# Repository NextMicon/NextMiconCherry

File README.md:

# NextMicon FPGA

**This repository has been split into per-board repositories and is archived.**
Development continues at
[NextMicon/cherry](https://github.com/NextMicon/cherry),
[NextMicon/grape](https://github.com/NextMicon/grape), and
[NextMicon/melon](https://github.com/NextMicon/melon).

NextMicon is a family of open-source FPGA development boards. Choose the compact Cherry to get started, or Grape for a larger FPGA and more I/O.

|       | [🍒 Cherry](boards/cherry/) | [🍇 Grape](boards/grape/)     | [🍈 Melon](boards/melon/)      |
| ----- | -------------------------- | ---------------------------- | ----------------------------- |
| FPGA  | Lattice iCE40HX8K-BG121    | AMD Spartan-7 XC7S50-CSGA324 | AMD Artix-7 XC7A100T-1FGG676C |
| Logic | 7,680 (4-input LUT)        | 32,600 (6-input LUT)         | 63,400 (6-input LUT)          |
| BRAM  | 128 Kbit                   | 2,700 Kbit                   | 4,860 Kbit                    |
| DSP   | —                          | 120                          | 240                           |
| GPIO  | 64                         | 128                          | 256                           |

## 🍒 NextMicon Cherry

**A compact board for learning and small projects.** Cherry is built around the Lattice iCE40HX8K-BG121, with 7,680 LUTs, 64 GPIO pins, native USB Full-Speed, and protected `boot` plus writable `user` FPGA images. The repository includes its KiCad PCB design, fabrication outputs, bootloader HDL, and host application.

[Explore Cherry →](boards/cherry/)

Cherry firmware can be managed with the [`nmb` CLI](flash/cli/README.md) or the
[Web Serial flasher](flash/web/README.md).

## 🍇 NextMicon Grape

**A mid-range board for multi-channel phased-array acoustic field generation.** Grape uses the AMD Spartan-7 XC7S50-CSGA324 with 128 GPIO outputs and a 128-Mbit QSPI flash. Firmware is built and programmed with a fully open-source Yosys, nextpnr-xilinx, Project X-Ray, and openFPGALoader stack. Its schematic and PCB are being migrated from the earlier Artix-7 prototype.

[Explore Grape →](boards/grape/)

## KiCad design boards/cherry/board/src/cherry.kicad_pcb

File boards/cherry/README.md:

# 🍒 NextMicon Cherry 🍒

FPGA Board for Beginners

## Repository layout

- [`board`](board/): KiCad design and fabrication outputs
- [`breakout`](breakout/): PMod breakout board
- [`firmware`](firmware/): FPGA HDL and constraints

## Schematic

## Specs

- FPGA: Lattice iCE40HX8K-BG121 (7680 LUTs, 9x9mm, 0.8mm pitch)
- GPIO: 64 pins (3.3V logic)
- PLL: 2x sysCLOCK PLL, external reference inputs broken out on J3 position 22 (PLL0_IN/PLL1_IN)
- Clock: 48MHz
- Flash: 32Mbit SPI Flash (3.5 MiB user-data area)
- Power: USB 5V → 3.3V → 1.2V
- Signal: 3.3V
- USB ESD Protection
- Switch: CRESET_B reset / USER buttons
- LED: PWR / PROG / USER0-USER3
- Board: 61mm x 31mm, 4-layer FR4

## Pinout

J2 and J3 are standard 2x24 headers. Each connector position `k` (1..24) has an
inner-row pad `2k-1` (odd) and an outer-row pad `2k` (even); the two rows carry
independent signals.

GPIOs are grouped in blocks of eight: D0-D3 sit on the inner row and D4-D7 sit
directly opposite on the outer row of the same four positions, so every block
forms one contiguous 2x4 window flanked by GND (inner) / 3V3 (outer) columns.
J2 carries GPIO_1..32 and J3 carries GPIO_33..64.

J2 (bottom edge, position 1 = USB side):

| Position | Inner row (odd pads) | Outer row (even pads) |
| -------- | -------------------- | --------------------- |
| 1        | 5V                   | 5V                    |
| 2        | 3V3                  | 3V3                   |
| 3        | CRESET_B             | 3V3                   |
| 4        | GND                  | 3V3                   |
| 5-8      | GPIO_1..4            | GPIO_5..8             |
| 9        | GND                  | 3V3                   |
| 10-13    | GPIO_9..12           | GPIO_13..16           |
| 14       | GND                  | 3V3                   |
| 15-18    | GPIO_17..20          | GPIO_21..24           |
| 19       | GND                  | 3V3                   |
| 20-23    | GPIO_25..28          | GPIO_29..32           |
| 24       | GND                  | 3V3                   |

J3 (top edge, position 24 = USB side):

| Position | Inner row (odd pads) | Outer row (even pads) |
| -------- | -------------------- | --------------------- |
| 1        | GND                  | 3V3                   |
| 2-5      | GPIO_33..36          | GPIO_37..40           |
| 6        | GND                  | 3V3                   |
| 7-10     | GPIO_41..44          | GPIO_45..48           |
| 11       | GND                  | 3V3                   |
| 12-15    | GPIO_49..52          | GPIO_53..56           |
| 16       | GND                  | 3V3                   |
| 17-20    | GPIO_57..60          | GPIO_61..64           |
| 21       | GND                  | 3V3                   |
| 22       | PLL0_IN              | PLL1_IN               |
| 23       | 3V3                  | 3V3                   |
| 24       | 5V                   | 5V                    |

| Header                          | Pins                                                                           |
| ------------------------------- | ------------------------------------------------------------------------------ |
| J4 (right edge, pin 1 = bottom) | 1 = GND, 2 = CRESET_B, 3 = QSPI_CS_B, 4 = QSPI_SCK, 5 = QSPI_IO0, 6 = QSPI_IO1 |

The breakout board ([`breakout/`](breakout/)) accepts the Cherry via female
pin sockets (J2/J3/J4 plug straight in) and brings the 64 GPIOs out as eight
standard Pmod ports (8 GPIO each), plus an SPI header and a power/CRESET
utility header.

## BOM

| Ref   | Part                                     | Package         | Description              | Cost  | Buy                                                                                           |
| ----- | ---------------------------------------- | --------------- | ------------------------ | ----- | --------------------------------------------------------------------------------------------- |
| U1    | [W25Q32JVSSIQ](../../parts/W25Q32JV.pdf) | SOIC-8 208mil   | 32Mbit SPI Flash         | -     | [digikey](https://www.digikey.com/en/products/result?keywords=W25Q32JVSSIQ)                   |
| U2    | [iCE40HX8K-BG121](../../parts/iCE40.pdf) | caBGA-121 0.8mm | FPGA 7680 LUTs           | -     | [digikey](https://www.digikey.com/en/products/result?keywords=ICE40HX8K-BG121)                |
| U3-U4 | [TPS62A02](../../parts/TPS62A02.pdf)     | SOT-23-6        | 2A DC-DC Converter       | $0.25 | [digikey](https://www.digikey.jp/ja/products/detail/texas-instruments/TPS62A02PDDCR/22147220) |
| D1    | USBLC6-2SC6                              | SOT-23-6        | USB ESD protection       | -     | [digikey](https://www.digikey.jp/ja/products/result?keywords=USBLC6-2SC6)                     |
| X1    | OXETDLJANF-48.000000MHz                  | 3.2x2.5mm       | 48MHz XO                 | -     | generic                                                                                       |
| FB1   | GZ2012D601TF                             | 0805            | Ferrite bead (USB VBUS)  | -     | [lcsc](https://www.lcsc.com/search?q=GZ2012D601TF)                                            |
| J1    | USB4085-GF-A                             | SMD 16pin       | USB-C connector          | $1.01 | [digikey](https://www.digikey.jp/ja/products/detail/gct/USB4085-GF-A/9859662)                 |
| J2-J3 | Pin header 2x24                          | 2.54mm Pitch    | GPIO                     | -     | generic                                                                                       |
| J4    | Pin header 1x06                          | 2.54mm Pitch    | External SPI programming | -     | generic                                                                                       |
### Passives

| Ref                       | Value                | Pkg  | Qty |
| ------------------------- | -------------------- | ---- | --- |
| C1,C3,C5,C14,C17          | 10uF                 | 0805 | 5   |
| C4,C6                     | 22uF                 | 0805 | 2   |
| C2,C7-C13,C15-C16,C18-C24 | 100nF               | 0402 | 17  |
| L1-L2                     | TFM201208ALD-1R0MTCA | 0805 | 2   |
| R1-R2                     | 5.1k                 | 0402 | 2   |
| R3,R5-R6                  | 100k                 | 0402 | 3   |
| R4                        | 22k                  | 0402 | 1   |
| R7                        | 1.5k                 | 0402 | 1   |
| R8-R9                     | 68                   | 0402 | 2   |
| R10-R13,R16-R17,R22-R23   | 10k                  | 0402 | 8   |
| R14,R18-R21,R24-R25       | 1k                   | 0402 | 7   |
| R15                       | 100                  | 0402 | 1   |
| D2-D4,D6-D7               | KT-0603R             | 0603 | 5   |
| D5                        | LED_AMBER_0603       | 0603 | 1   |
| SW1-SW2                   | TS-1187A-B-A-B       | SMD  | 2   |
| JP1-JP2                   | Solder jumper        | SMD  | 2   |

## Build

Toolchain: [Yosys](https://github.com/YosysHQ/yosys) + [nextpnr-ice40](https://github.com/YosysHQ/nextpnr) + [icestorm](https://github.com/YosysHQ/icestorm)

The pin and timing constraint files are
[`firmware/cherry.pcf`](firmware/cherry.pcf) and
[`firmware/cherry.sdc`](firmware/cherry.sdc). Yosys produces the JSON netlist
and nextpnr consumes the PCF/SDC:

```bash
mkdir -p build
yosys -p 'synth_ice40 -top top -json build/top.json' rtl/top.v
nextpnr-ice40 --hx8k --package bg121 --freq 48 \
  --json build/top.json --pcf firmware/cherry.pcf --sdc firmware/cherry.sdc \
  --asc build/top.asc
icepack build/top.asc build/top.bin
```

Only ports present in the top-level HDL need to be used; nextpnr reports the
other PCF entries as harmless `unmatched constraint` warnings. Keep `clk_48m`
as an input. The commented SPI-flash constraints are intentionally reserved
because the flash and FPGA configuration controller share those four nets.

For recovery programming, power the board from USB and connect a 3.3V SPI
programmer to J4. Hold `CRESET_B` low while accessing the W25Q32, then release
it to boot the newly written image.

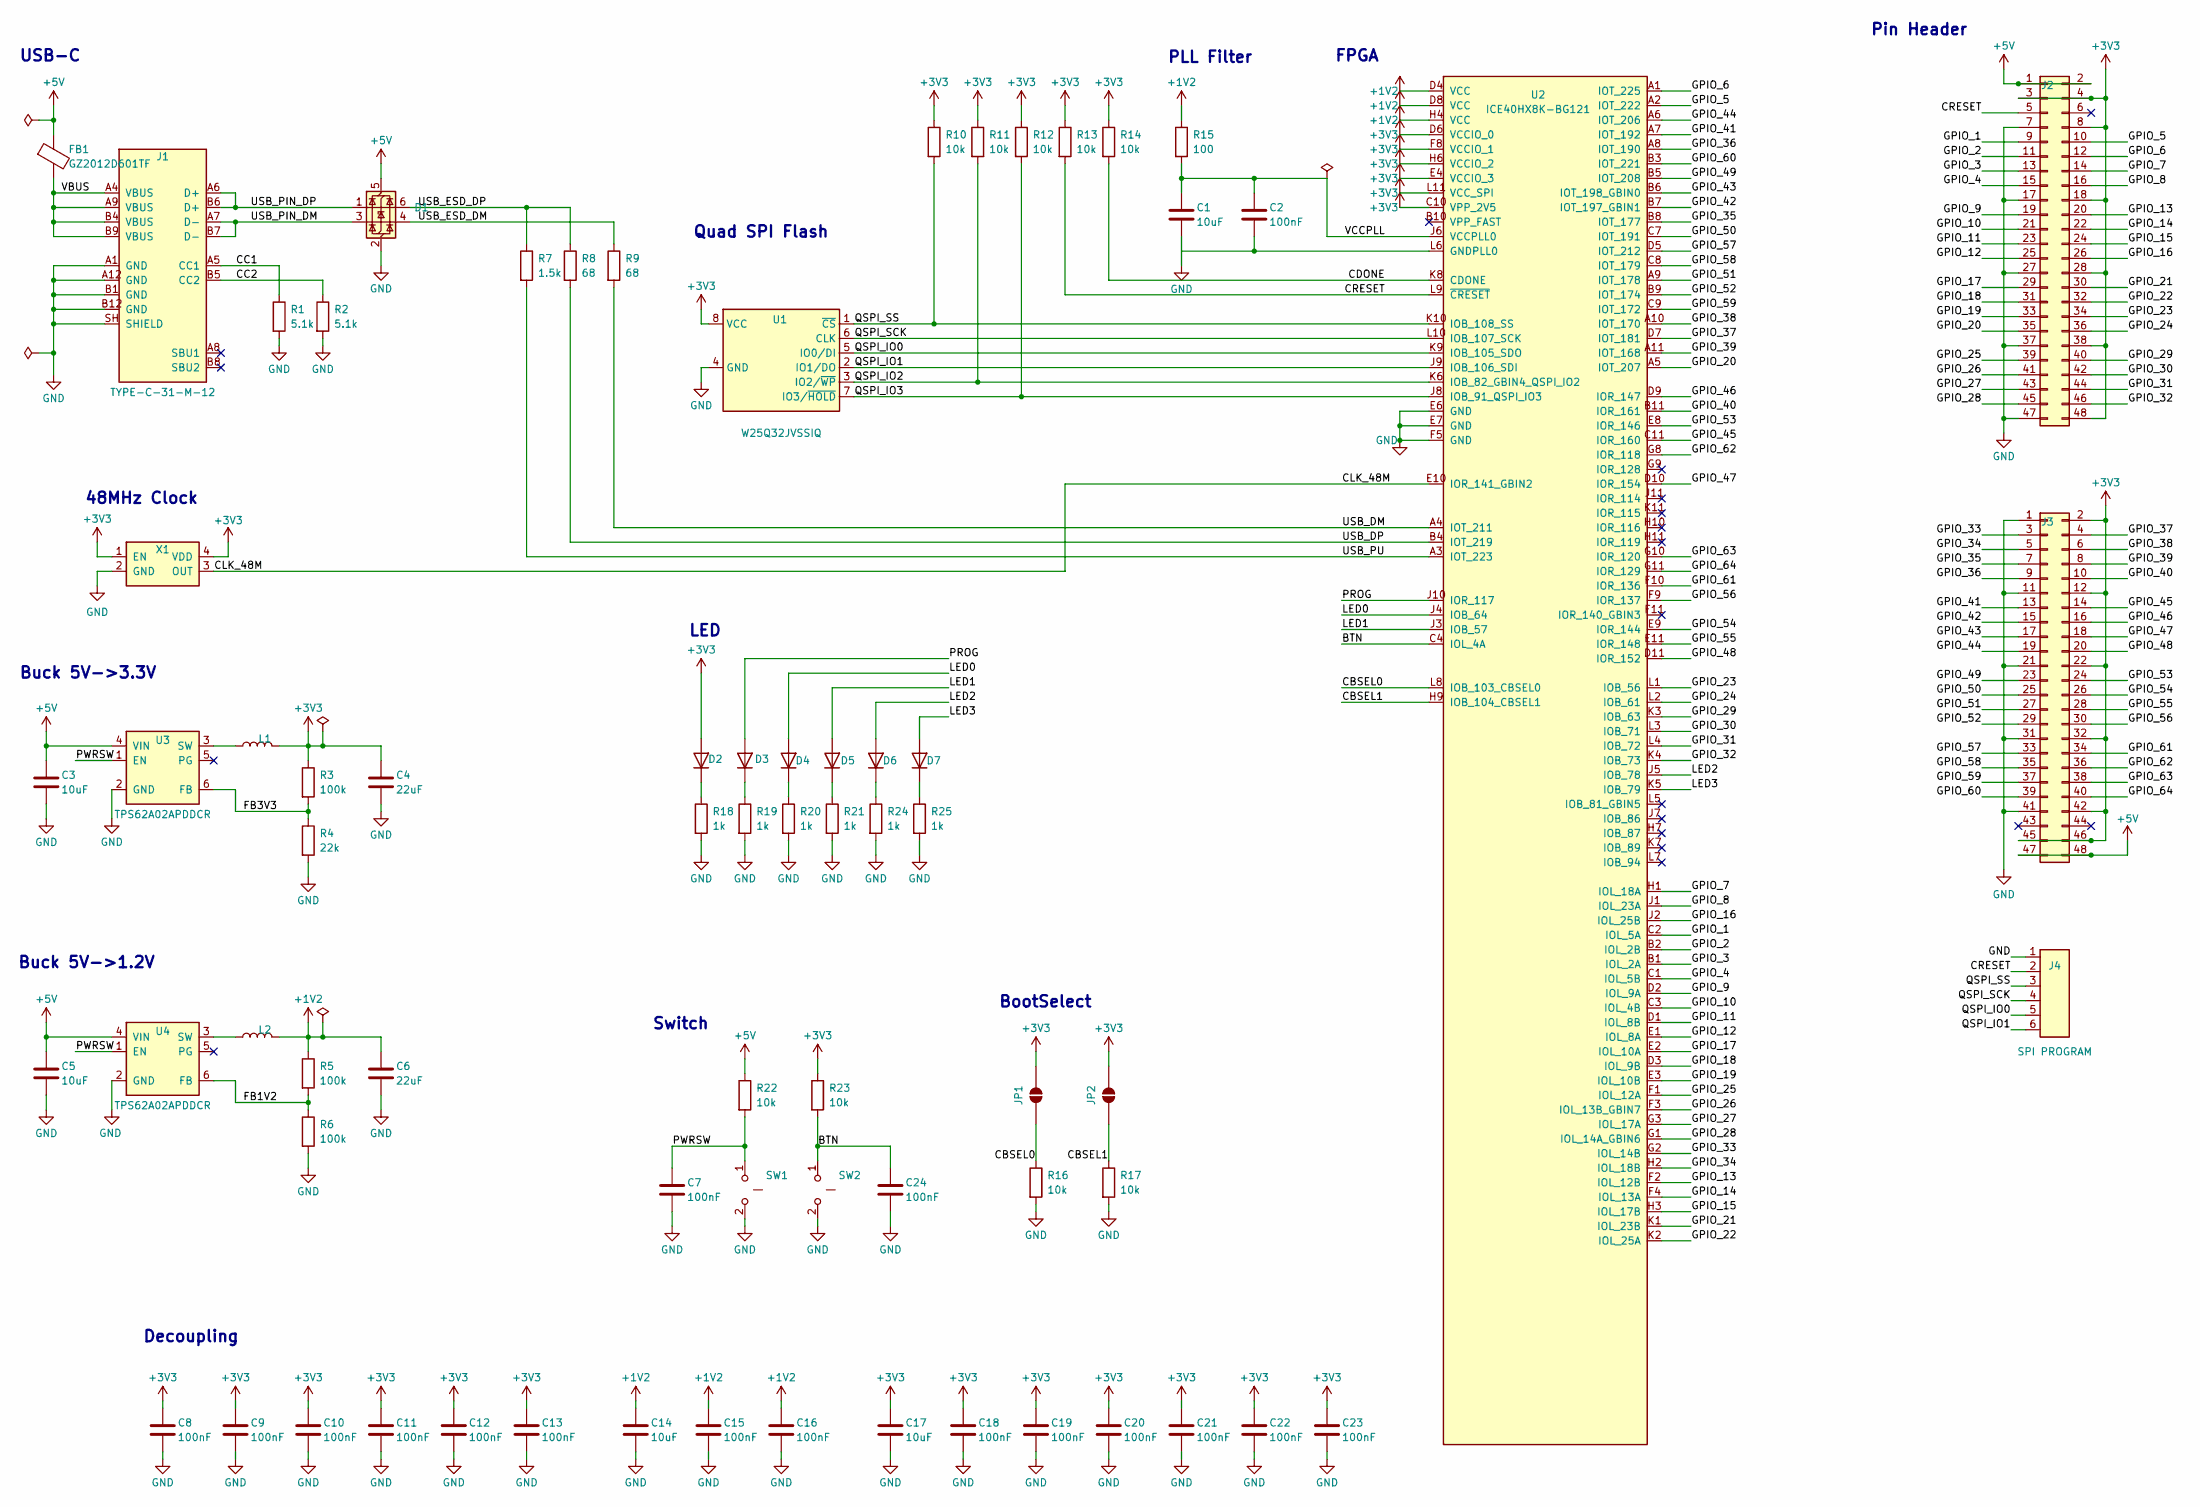
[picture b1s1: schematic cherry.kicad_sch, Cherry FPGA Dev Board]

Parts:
C1, C3, C5, C14, C17: 10uF; C_0805_2012Metric; LCSC C15850
C2, C7, C8, C9, C10, C11, C12, C13, C15, C16, C18, C19, C20, C21, C22, C23, C24: 100nF; C_0402_1005Metric; LCSC C1525
C4, C6: 22uF; C_0805_2012Metric; LCSC C45783
D1: USBLC6-2SC6; SOT-23-6; LCSC C2687116
D2, D3, D4, D6, D7: KT-0603R; LED_0603_1608Metric; LCSC C2286
D5: LED_AMBER_0603; LED_0603_1608Metric
FB1: GZ2012D601TF; L_0805_2012Metric; LCSC C1017
J1: TYPE-C-31-M-12; USB_C_Receptacle_Hroparts_TYPE-C-31-M-12; LCSC C165948
J2, J3: Conn_02x24_Odd_Even; PinHeader_2x24_P2.54mm_Vertical
J4: SPI PROGRAM; PinHeader_1x06_P2.54mm_Vertical
JP1, JP2: USER; SolderJumper-2_P1.3mm_Open_RoundedPad1.0x1.5mm
L1, L2: TFM201208ALD-1R0MTCA; L_TDK_TFM201208ALD; LCSC C433051
R1, R2: 5.1k; R_0402_1005Metric; LCSC C25905
R3, R5, R6: 100k; R_0402_1005Metric; LCSC C25741
R4: 22k; R_0402_1005Metric; LCSC C25768
R7: 1.5k; R_0402_1005Metric; LCSC C25117
R8, R9: 68; R_0402_1005Metric; LCSC C25117
R10, R11, R12, R13, R16, R17, R23: 10k; R_0402_1005Metric; LCSC C25744
R14: 10k; R_0402_1005Metric; LCSC C11702
R15: 100; R_0402_1005Metric; LCSC C25076
R18, R19, R20, R21, R24, R25: 1k; R_0402_1005Metric; LCSC C11702
R22: 10k; R_0402_1005Metric; LCSC C25741
SW1: TS-1187A-B-A-B; SW_Tactile_XKB_TS-1187A; LCSC C318884
SW2: USER; SW_Tactile_XKB_TS-1187A; LCSC C318884
U1: W25Q32JVSSIQ; SOIC-8_5.3x5.3mm_P1.27mm; LCSC C179173
U2: ICE40HX8K-BG121; BGA-121_9.0x9.0mm_Layout11x11_P0.8mm_Ball0.4mm_Pad0.35mm_NS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
U3, U4: TPS62A02APDDCR; SOT-23-6; LCSC C25687169
X1: OXETDLJANF-48.000000MHz; Oscillator_SMD_Taitien_OX_3.2x2.5mm; LCSC C5173414

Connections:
+1V2: C6.1, C14.1, C15.1, C16.1, L2.2, R5.1, R15.1, U2.D4 (VCC), U2.D8 (VCC), U2.H4 (VCC), U2.H8 (VCC)
+3V3: C4.1, C8.1, C9.1, C10.1, C11.1, C12.1, C13.1, C17.1, C18.1, C19.1, C20.1, C21.1, C22.1, C23.1, D2.2 (A), J2.3, J2.4, J2.8, J2.18, J2.28, J2.38, J2.48, J3.2, J3.12, J3.22, J3.32, J3.42, J3.45, J3.46, JP1.2 (B), JP2.2 (B), L1.2, R3.1, R10.1, R11.1, R12.1, R13.1, R14.1, R23.1, U1.8 (VCC), U2.C10 (VPP_2V5), U2.D6 (VCCIO_0), U2.E4 (VCCIO_3), U2.F8 (VCCIO_1), U2.G4 (VCCIO_3), U2.H6 (VCCIO_2), U2.L11 (VCC_SPI), X1.1 (EN), X1.4 (VDD)
+5V: C3.1, C5.1, D1.5 (VBUS), FB1.1, J2.1, J2.2, J3.47, J3.48, R22.1, U3.4 (VIN), U4.4 (VIN)
/BTN: C24.1, R23.2, SW2.1, U2.C4 (IOL_4A)
/CBSEL0: JP1.1 (A), R16.1, U2.L8 (IOB_103_CBSEL0)
/CBSEL1: JP2.1 (A), R17.1, U2.H9 (IOB_104_CBSEL1)
/CC1: J1.A5 (CC1), R1.1
/CC2: J1.B5 (CC2), R2.1
/CDONE: R14.2, U2.K8 (CDONE)
/CLK_48M: U2.E10 (IOR_141_GBIN2), X1.3 (OUT)
/CRESET: J2.5, J4.2, R13.2, U2.L9 (~CRESET)
/FB1V2: R5.2, R6.1, U4.6 (FB)
/FB3V3: R3.2, R4.1, U3.6 (FB)
/GPIO_1: J2.9, U2.C2 (IOL_5A)
/GPIO_2: J2.11, U2.B2 (IOL_2B)
/GPIO_3: J2.13, U2.B1 (IOL_2A)
/GPIO_4: J2.15, U2.C1 (IOL_5B)
/GPIO_5: J2.10, U2.A2 (IOT_222)
/GPIO_6: J2.12, U2.A1 (IOT_225)
/GPIO_7: J2.14, U2.H1 (IOL_18A)
/GPIO_8: J2.16, U2.J1 (IOL_23A)
/GPIO_9: J2.19, U2.D2 (IOL_9A)
/GPIO_10: J2.21, U2.C3 (IOL_4B)
/GPIO_11: J2.23, U2.D1 (IOL_8B)
/GPIO_12: J2.25, U2.E1 (IOL_8A)
/GPIO_13: J2.20, U2.F2 (IOL_12B)
/GPIO_14: J2.22, U2.F4 (IOL_13A)
/GPIO_15: J2.24, U2.H3 (IOL_17B)
/GPIO_16: J2.26, U2.J2 (IOL_25B)
/GPIO_17: J2.29, U2.E2 (IOL_10A)
/GPIO_18: J2.31, U2.D3 (IOL_9B)
/GPIO_19: J2.33, U2.E3 (IOL_10B)
/GPIO_20: J2.35, U2.A5 (IOT_207)
/GPIO_21: J2.30, U2.K1 (IOL_23B)
/GPIO_22: J2.32, U2.K2 (IOL_25A)
/GPIO_23: J2.34, U2.L1 (IOB_56)
/GPIO_24: J2.36, U2.L2 (IOB_61)
/GPIO_25: J2.39, U2.F1 (IOL_12A)
/GPIO_26: J2.41, U2.F3 (IOL_13B_GBIN7)
/GPIO_27: J2.43, U2.G3 (IOL_17A)
/GPIO_28: J2.45, U2.G1 (IOL_14A_GBIN6)
/GPIO_29: J2.40, U2.K3 (IOB_63)
/GPIO_30: J2.42, U2.L3 (IOB_71)
/GPIO_31: J2.44, U2.L4 (IOB_72)
/GPIO_32: J2.46, U2.K4 (IOB_73)
/GPIO_33: J3.3, U2.G2 (IOL_14B)
/GPIO_34: J3.5, U2.H2 (IOL_18B)
/GPIO_35: J3.7, U2.B8 (IOT_177)
/GPIO_36: J3.9, U2.A8 (IOT_190)
/GPIO_37: J3.4, U2.D7 (IOT_181)
/GPIO_38: J3.6, U2.A10 (IOT_170)
/GPIO_39: J3.8, U2.A11 (IOT_168)
/GPIO_40: J3.10, U2.B11 (IOR_161)
/GPIO_41: J3.13, U2.A7 (IOT_192)
/GPIO_42: J3.15, U2.B7 (IOT_197_GBIN1)
/GPIO_43: J3.17, U2.B6 (IOT_198_GBIN0)
/GPIO_44: J3.19, U2.A6 (IOT_206)
/GPIO_45: J3.14, U2.C11 (IOR_160)
/GPIO_46: J3.16, U2.D9 (IOR_147)
/GPIO_47: J3.18, U2.D10 (IOR_154)
/GPIO_48: J3.20, U2.D11 (IOR_152)
/GPIO_49: J3.23, U2.B5 (IOT_208)
/GPIO_50: J3.25, U2.C7 (IOT_191)
/GPIO_51: J3.27, U2.A9 (IOT_178)
/GPIO_52: J3.29, U2.B9 (IOT_174)
/GPIO_53: J3.24, U2.E8 (IOR_146)
/GPIO_54: J3.26, U2.E9 (IOR_144)
/GPIO_55: J3.28, U2.E11 (IOR_148)
/GPIO_56: J3.30, U2.F9 (IOR_137)
/GPIO_57: J3.33, U2.D5 (IOT_212)
/GPIO_58: J3.35, U2.C8 (IOT_179)
/GPIO_59: J3.37, U2.C9 (IOT_172)
/GPIO_60: J3.39, U2.B3 (IOT_221)
/GPIO_61: J3.34, U2.F10 (IOR_136)
/GPIO_62: J3.36, U2.G8 (IOR_118)
/GPIO_63: J3.38, U2.G10 (IOR_120)
/GPIO_64: J3.40, U2.G11 (IOR_129)
/LED0: D4.2 (A), U2.J4 (IOB_64)
/LED1: D5.2 (A), U2.J3 (IOB_57)
/LED2: D6.2 (A), U2.J5 (IOB_78)
/LED3: D7.2 (A), U2.K5 (IOB_79)
/PROG: D3.2 (A), U2.J10 (IOR_117)
/PWRSW: C7.1, R22.2, SW1.1, U3.1 (EN), U4.1 (EN)
/QSPI_IO0: J4.5, U1.5 (IO0/DI), U2.K9 (IOB_105_SDO)
/QSPI_IO1: J4.6, U1.2 (IO1/DO), U2.J9 (IOB_106_SDI)
/QSPI_IO2: R11.2, U1.3 (IO2/~WP), U2.K6 (IOB_82_GBIN4_QSPI_IO2)
/QSPI_IO3: R12.2, U1.7 (IO3/~HOLD), U2.J8 (IOB_91_QSPI_IO3)
/QSPI_SCK: J4.4, U1.6 (CLK), U2.L10 (IOB_107_SCK)
/QSPI_SS: J4.3, R10.2, U1.1 (~CS), U2.K10 (IOB_108_SS)
/USB_DM: R9.2, U2.A4 (IOT_211)
/USB_DP: R8.2, U2.B4 (IOT_219)
/USB_ESD_DM: D1.4 (I/O2), R9.1
/USB_ESD_DP: D1.6 (I/O1), R7.1, R8.1
/USB_PIN_DM: D1.3 (I/O2), J1.A7 (D-), J1.B7 (D-)
/USB_PIN_DP: D1.1 (I/O1), J1.A6 (D+), J1.B6 (D+)
/USB_PU: R7.2, U2.A3 (IOT_223)
/VBUS: FB1.2, J1.A4 (VBUS), J1.A9 (VBUS), J1.B4 (VBUS), J1.B9 (VBUS)
/VCCPLL: C1.1, C2.1, R15.2, U2.C6 (VCCPLL1), U2.J6 (VCCPLL0)
GND: C1.2, C2.2, C3.2, C4.2, C5.2, C6.2, C7.2, C8.2, C9.2, C10.2, C11.2, C12.2, C13.2, C14.2, C15.2, C16.2, C17.2, C18.2, C19.2, C20.2, C21.2, C22.2, C23.2, C24.2, D1.2 (GND), J1.A1 (GND), J1.A12 (GND), J1.B1 (GND), J1.B12 (GND), J1.SH (SHIELD), J2.7, J2.17, J2.27, J2.37, J2.47, J3.1, J3.11, J3.21, J3.31, J3.41, J4.1, R1.2, R2.2, R4.2, R6.2, R16.2, R17.2, R18.2, R19.2, R20.2, R21.2, R24.2, R25.2, SW1.2, SW2.2, U1.4 (GND), U2.C5 (GNDPLL1), U2.E5 (GND), U2.E6 (GND), U2.E7 (GND), U2.F5 (GND), U2.F6 (GND), U2.F7 (GND), U2.G5 (GND), U2.G6 (GND), U2.G7 (GND), U2.H5 (GND), U2.L6 (GNDPLL0), U3.2 (GND), U4.2 (GND), X1.2 (GND)
unnamed: D2.1 (K), R18.1
unnamed: D3.1 (K), R19.1
unnamed: D4.1 (K), R20.1
unnamed: D5.1 (K), R21.1
unnamed: D6.1 (K), R24.1
unnamed: D7.1 (K), R25.1
unnamed: L1.1, U3.3 (SW)
unnamed: L2.1, U4.3 (SW)

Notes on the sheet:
Switch
Buck 5V->3.3V
BootSelect
Pin Header
Buck 5V->1.2V
FPGA
PLL Filter
LED
USB-C
48MHz Clock
Quad SPI Flash
Decoupling

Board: 4 copper layers, 72 parts (2 on the bottom side), 107 nets, no tracks yet.

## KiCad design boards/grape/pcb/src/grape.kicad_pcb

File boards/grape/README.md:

# 🍇 NextMicon Grape 🍇

Mid-range FPGA board for multi-channel phased-array acoustic field generation.

## Repository layout

- [`board`](board/): KiCad design and fabrication outputs
- [`breakout`](breakout/): breakout and test-fixture designs
- [`firmware`](firmware/): FPGA HDL and constraints

## Schematic

## Target specs

- FPGA: AMD Spartan-7 `XC7S50-1CSGA324C`
  - 52,160 logic cells
  - 120 DSP48E1 slices
  - 2,764,800 bits of Block RAM
  - 210 user I/O pins in the CSGA324 package
- GPIO: 128 pins reserved for phased-array channel outputs
- GPIO logic level: 3.3 V
- Channel count: 128 channels with one GPIO per channel
- Clock: 100 MHz onboard oscillator; USB 48 MHz and application clocks generated by MMCM/PLL
- Configuration: 128-Mbit QSPI flash
- USB: USB-C for power and control
- Power: USB 5 V input with FPGA core, auxiliary, and I/O rails
- Recovery: external JTAG and `PROGRAM_B`
- FPGA package: CSGA324, 15 mm x 15 mm, 0.8 mm ball pitch
- GPIO connectors: four 2x24, 2.54 mm headers using the Cherry 8-pin group geometry
- Placement study: 140 mm x 70 mm, four layers, deliberately unrouted
- Final regulator sizing: pending electrical implementation verification

The 128 GPIO signals are logic-level timing outputs. External level shifters,
gate drivers, and power stages must be used to drive acoustic transducers; the
transducers must not be driven directly from FPGA pins.

## Intended architecture

Grape receives phase and optional amplitude parameters from a host and produces
phase-synchronous waveforms for up to 128 acoustic channels. The baseline
firmware uses a common phase accumulator and per-channel phase offsets stored in
Block RAM. All channel parameters are double-buffered so that an update can be
applied to every output on the same clock boundary.

The baseline design targets externally calculated phase values. Coordinate-to-
phase calculation, multi-focus synthesis, and closed-loop field control are
reserved for higher-end boards such as Melon.

## I/O allocation

The CSGA324 package provides up to 210 user I/O pins. The checked allocation is:

| Function                        |      Pins | Notes                                    |
| ------------------------------- | --------: | ---------------------------------------- |
| Phased-array outputs            |       128 | Banks 15, 34 and 35; 3.3 V               |
| Clock and USB                   |         3 | Bank 14; 100 MHz plus USB D+/D-           |
| User strap, button and LEDs     |         4 | Bank 14                                   |
| Configuration and JTAG         | Dedicated | Bank 0 and Bank 14 configuration pins     |

The generated and machine-checked mapping is [`board/pinout.csv`](board/pinout.csv).
Each set of 32 GPIOs uses one 2x24 header. As on Cherry, every group of eight is
a contiguous 2x4 window with four inner-row and four outer-row signals; group
separators carry GND on the inner row and 3.3 V on the outer row. The mapping
is generated from AMD's official `xc7s50csga324pkg.csv` by
[`board/tools/generate_pinout.py`](board/tools/generate_pinout.py).

If complementary high-side/low-side signals are generated directly by the
FPGA, 128 GPIOs provide 64 channels. The preferred 128-channel implementation
uses one FPGA output per channel and generates complementary drive signals in
the external driver stage.

## Current hardware status

The existing KiCad files under [`board/src`](board/src) describe the earlier
Artix-7 `XC7A35T-1FTG256C`, 56-GPIO prototype. They do not yet implement this
Spartan-7 target specification. The schematic, PCB, power tree, FPGA symbol,
pin assignments, decoupling, and constraints must be migrated to
`XC7S50-1CSGA324C` before fabrication.

The replacement six-unit KiCad symbol
[`board/src/grape-fpga.kicad_sym`](board/src/grape-fpga.kicad_sym) is generated
from AMD's production `xc7s50csga324pkg.csv`; it contains all 324 unique package
balls and uses the matching `Package_BGA:Xilinx_CSGA324` footprint. Regenerate
it with [`board/tools/generate_fpga_symbol.py`](board/tools/generate_fpga_symbol.py).
The symbol and checked 128-GPIO pinout are ready; integration into the new
schematic and PCB is in progress. The old schematic and placement board remain
non-fabrication references until that migration is complete.

## Build

Grape is developed with a fully open-source FPGA toolchain. AMD Vivado is not
used or required by the intended build and programming workflow.

- HDL synthesis: [Yosys](https://github.com/YosysHQ/yosys)
- Place and route: [nextpnr-xilinx](https://github.com/gatecat/nextpnr-xilinx)
- 7-series device database and bitstream support:
  [Project X-Ray](https://github.com/f4pga/prjxray)
- Timing constraints: XDC
- Bitstream and QSPI programming:
  [openFPGALoader](https://github.com/trabucayre/openFPGALoader)

The repository will provide reproducible command-line build scripts and pinned
tool/database revisions. The exact `xc7s50csga324-1` part is present in the
Project X-Ray database; the complete build and programming flow must still be
validated on Grape hardware before release.

The final top-level port names, XDC pin constraints, clock constraints, and
bitstream/flash programming procedure will be documented after the schematic
and connector pinout are fixed.

## Before PCB fabrication

- Assign all 128 outputs using the official CSGA324 package pin file.
- Reserve configuration, JTAG, clock, USB/control, and debug pins first.
- Check every I/O bank voltage and the simultaneous-switching-output limits.
- Establish a worst-case power budget from AMD data-sheet values and measured
  activity from the open-source implementation.
- Verify regulator capacity, startup sequencing, thermal margin, and decoupling.
- Validate that the external driver input load is within the FPGA I/O limits.
- Add source-series termination where signal-integrity analysis requires it.
- Complete schematic ERC and routed-board DRC before generating fabrication data.

## Primary references

- [AMD DS189: Spartan-7 FPGAs Data Sheet](https://docs.amd.com/v/u/en-US/ds189-spartan-7-data-sheet)
- [AMD DS180: 7 Series FPGAs Overview](https://docs.amd.com/v/u/en-US/ds180_7Series_Overview)
- [AMD UG470: 7 Series FPGAs Configuration User Guide](https://docs.amd.com/v/u/en-US/ug470_7Series_Config)
- [AMD UG475: 7 Series FPGAs Packaging and Pinout](https://docs.amd.com/v/u/en-US/ug475_7Series_Pkg_Pinout)
- [AMD UG479: 7 Series DSP48E1 Slice User Guide](https://docs.amd.com/v/u/en-US/ug479_7Series_DSP48E1)
- [AMD UG483: 7 Series FPGAs PCB Design Guide](https://docs.amd.com/v/u/en-US/ug483_7Series_PCB)

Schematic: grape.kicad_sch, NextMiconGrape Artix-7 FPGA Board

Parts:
C1, C15: 1uF; C_0603_1608Metric
C2: 4.7nF TUNE; C_0402_1005Metric
C3, C5, C8, C11, C20: 10uF; C_0805_2012Metric
C4, C16, C17, C18: 100nF; C_0402_1005Metric
C6, C7, C9, C10, C12, C13: 22uF; C_0805_2012Metric
C14: 4.7nF; C_0402_1005Metric
C19: 470nF; C_0402_1005Metric
C21: 100uF; C_1210_3225Metric
C22, C29, C35, C36, C37, C38, C39: 47uF; C_1210_3225Metric
C23, C24, C30, C31, C40, C41, C42, C43, C44, C45, C46, C47: 4.7uF; C_0603_1608Metric
C25, C26, C27, C28, C32, C33, C34, C48, C49, C50, C51, C52, C53, C54, C55, C56, C57, C58, C59, C60, C61, C62, C63: 0.47uF; C_0402_1005Metric
D1: 1 LED; LED_0603_1608Metric
D2: CFG DONE; LED_0603_1608Metric
D3: 3 LED; LED_0603_1608Metric
D4: 4 LED; LED_0603_1608Metric
D5: 5 LED; LED_0603_1608Metric
F1: 1.1A hold; Fuse_1206_3216Metric
FB1, FB2: 600R@100MHz; L_0805_2012Metric
J1: USB-C USB2 Device; USB_C_Receptacle_GCT_USB4085
J2: GPIO 0-27; PinHeader_2x20_P2.54mm_Vertical
J3: GPIO 28-55; PinHeader_2x20_P2.54mm_Vertical
J4: JTAG; PinHeader_1x06_P2.54mm_Vertical
JP1: GOLDEN_LOCK (fit for x1); PinHeader_1x02_P2.54mm_Vertical
L1, L2, L3: 1uH >=2.5A; L_0805_2012Metric
Q1: BSS138; SOT-23
R1, R4, R7, R10: 100k; R_0402_1005Metric
R2: 66.5k 1%; R_0402_1005Metric
R3, R5, R8: 100k 1%; R_0402_1005Metric
R6: 49.9k 1%; R_0402_1005Metric
R9: 22.1k 1%; R_0402_1005Metric
R11, R49, R53, R54, R55, R56, R71, R73, R74, R75: 1k; R_0402_1005Metric
R20, R21, R40, R41, R42, R43, R44, R45: 22R TUNE; R_0402_1005Metric
R22: 1.5k; R_0402_1005Metric
R23, R24: 5.1k; R_0402_1005Metric
R25: 82k; R_0402_1005Metric
R26: 68k; R_0402_1005Metric
R27: 1M; R_0402_1005Metric
R46: 2.4k; R_0402_1005Metric
R47, R48, R50, R51, R52: 4.7k; R_0402_1005Metric
R57, R58, R59: 0R; R_0402_1005Metric
R60, R61: 10k; R_0402_1005Metric
SW1: IMAGE[1:0]; SW_DIP_SPSTx02_Slide_Omron_A6H-2101_W6.15mm_P1.27mm
SW2: COLD RESET; SW_Push_1P1T_NO_CK_KMR2
SW3: PROGRAM; SW_Push_1P1T_NO_CK_KMR2
U1: XC7A35T-1FTG256C; Xilinx_FTG256
U2, U3, U4: TPS62A02DRL; SOT-563
U5: W25Q128JVSIQ; SOIC-8_5.3x5.3mm_P1.27mm
U6: USBLC6-2SC6; SOT-23-6
U7: TPS22917DBV; SOT-23-6
X1: ASE-48.000MHz; Oscillator_SMD_Abracon_ASE-4Pin_3.2x2.5mm

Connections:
/+1V0: C6.1, C7.1, C21.1, C22.1, C23.1, C24.1, C25.1, C26.1, C27.1, C28.1, L1.2, R2.1, U1.E10 (VCCBRAM), U1.F7 (VCCINT), U1.F9 (VCCINT), U1.F11 (VCCBRAM), U1.G6 (VCCINT), U1.H9 (VCCINT), U1.J6 (VCCINT), U1.K9 (VCCINT), U1.L8 (VCCINT)
/+1V0_FB: R2.2, R3.1, U2.5 (FB)
/+1V0_SW: L1.1, U2.2 (SW)
/+1V8: C9.1, C10.1, C29.1, C30.1, C31.1, C32.1, C33.1, C34.1, FB1.1, L2.2, R5.1, U1.G10 (VCCAUX), U1.J10 (VCCAUX), U1.K11 (VCCAUX), U1.L10 (VCCAUX)
/+1V8A: C18.1, C19.1, C20.1, FB1.2, U1.G8 (VCCADC_0)
/+1V8_FB: R5.2, R6.1, U3.5 (FB)
/+1V8_SW: L2.1, U3.2 (SW)
/+3V3: C12.1, C13.1, C16.1, C17.1, C35.1, C36.1, C37.1, C38.1, C39.1, C40.1, C41.1, C42.1, C43.1, C44.1, C45.1, C46.1, C47.1, C48.1, C49.1, C50.1, C51.1, C52.1, C53.1, C54.1, C55.1, C56.1, C57.1, C58.1, C59.1, C60.1, C61.1, C62.1, C63.1, J2.1, J2.21, J2.39, J3.1, J3.21, J3.39, J4.1, L3.2, R8.1, R46.1, R47.1, R48.1, R49.1, R50.1, R51.1, R52.1, R53.1, R56.1, R57.1, R71.1, SW1.3, SW1.4, U1.A6 (VCCO_35), U1.A16 (VCCO_15), U1.B3 (VCCO_35), U1.B13 (VCCO_15), U1.C10 (VCCO_15), U1.D7 (VCCO_35), U1.E4 (VCCO_35), U1.E14 (VCCO_15), U1.F1 (VCCO_35), U1.H15 (VCCO_15), U1.J2 (VCCO_35), U1.J12 (VCCO_15), U1.L6 (VCCO_0), U1.L16 (VCCO_14), U1.M3 (VCCO_34), U1.M13 (VCCO_14), U1.N10 (VCCO_14), U1.P7 (VCCO_14), U1.R4 (VCCO_34), U1.R14 (VCCO_14), U1.T1 (VCCO_34), U1.T11 (VCCO_14), U5.8 (VCC), X1.1 (EN), X1.4 (Vdd)
/+3V3_FB: R8.2, R9.1, U4.5 (FB)
/+3V3_SW: L3.1, U4.2 (SW)
/+5V: C3.1, C5.1, C8.1, C11.1, J2.2, J2.40, J3.2, J3.40, R1.1, R4.1, R7.1, R10.1, R11.2, U2.3 (VIN), U3.3 (VIN), U4.3 (VIN), U7.6 (VOUT)
/AGND: C18.2, C19.2, C20.2, FB2.2, R58.1, R59.1, U1.G7 (GNDADC_0)
/CFGBVS_3V3: R57.2, U1.E7 (CFGBVS_0)
/CLK48: U1.E3 (IO_L11P_T1_SRCC_35), X1.3 (OUT)
/D1_A: D1.2 (A), R71.2
/D3_A: D3.2 (A), R73.2
/D4_A: D4.2 (A), R74.2
/D5_A: D5.2 (A), R75.2
/DONE: Q1.1 (G), R50.2, U1.H10 (DONE_0)
/DONE_LED_A: D2.2 (A), R56.2
/DONE_LED_K: D2.1 (K), Q1.3 (D)
/EN_1V8: R4.2, U2.6 (PG), U3.4 (EN)
/EN_3V3: R7.2, U3.6 (PG), U4.4 (EN)
/GND: C1.2, C3.2, C4.2, C5.2, C6.2, C7.2, C8.2, C9.2, C10.2, C11.2, C12.2, C13.2, C14.2, C15.2, C16.2, C17.2, C21.2, C22.2, C23.2, C24.2, C25.2, C26.2, C27.2, C28.2, C29.2, C30.2, C31.2, C32.2, C33.2, C34.2, C35.2, C36.2, C37.2, C38.2, C39.2, C40.2, C41.2, C42.2, C43.2, C44.2, C45.2, C46.2, C47.2, C48.2, C49.2, C50.2, C51.2, C52.2, C53.2, C54.2, C55.2, C56.2, C57.2, C58.2, C59.2, C60.2, C61.2, C62.2, C63.2, D1.1 (K), D3.1 (K), D4.1 (K), D5.1 (K), FB2.1, J1.A1 (GND), J1.A12 (GND), J1.B1 (GND), J1.B12 (GND), J2.11, J2.12, J2.22, J2.31, J2.32, J2.37, J2.38, J3.11, J3.12, J3.22, J3.31, J3.32, J3.37, J3.38, J4.2, JP1.2 (B), Q1.2 (S), R3.2, R6.2, R9.2, R23.2, R24.2, R26.2, R27.2, R54.2, R55.2, R60.2, R61.2, SW2.2, SW3.2, U1.A1 (GND), U1.A11 (GND), U1.B8 (GND), U1.C5 (GND), U1.C15 (GND), U1.D2 (GND), U1.D12 (GND), U1.E9 (GND), U1.F6 (GND), U1.F8 (VCCBATT_0), U1.F10 (GND), U1.F16 (GND), U1.G3 (GND), U1.G9 (GND), U1.G13 (GND), U1.H6 (GND), U1.J9 (GND), U1.J11 (GND), U1.K4 (GND), U1.K6 (GND), U1.K14 (GND), U1.L1 (GND), U1.L11 (GND), U1.M8 (GND), U1.N5 (GND), U1.N15 (GND), U1.P2 (GND), U1.P12 (GND), U1.R9 (GND), U1.T6 (GND), U1.T16 (GND), U2.1 (GND), U3.1 (GND), U4.1 (GND), U5.4 (GND), U6.2 (GND), U7.2 (GND), X1.2 (GND)
/GPIO_00: J2.3, U1.B1 (IO_L9N_T1_DQS_AD7N_35)
/GPIO_01: J2.4, U1.B2 (IO_L8P_T1_AD14P_35)
/GPIO_02: J2.5, U1.C1 (IO_L9P_T1_DQS_AD7P_35)
/GPIO_03: J2.6, U1.C2 (IO_L7N_T1_AD6N_35)
/GPIO_04: J2.7, U1.C3 (IO_L7P_T1_AD6P_35)
/GPIO_05: J2.8, U1.C4 (IO_L12N_T1_MRCC_35)
/GPIO_06: J2.9, U1.C6 (IO_L5N_T0_AD13N_35)
/GPIO_07: J2.10, U1.C7 (IO_L5P_T0_AD13P_35)
/GPIO_08: J2.13, U1.D1 (IO_L10N_T1_AD15N_35)
/GPIO_09: J2.14, U1.D3 (IO_L11N_T1_SRCC_35)
/GPIO_10: J2.15, U1.D4 (IO_L12P_T1_MRCC_35)
/GPIO_11: J2.16, U1.D5 (IO_L6N_T0_VREF_35)
/GPIO_12: J2.17, U1.D6 (IO_L6P_T0_35)
/GPIO_13: J2.18, U1.E1 (IO_L15N_T2_DQS_35)
/GPIO_14: J2.19, U1.E2 (IO_L10P_T1_AD15P_35)
/GPIO_15: J2.20, U1.E5 (IO_L13N_T2_MRCC_35)
/GPIO_16: J2.23, U1.E6 (IO_0_35)
/GPIO_17: J2.24, U1.F2 (IO_L15P_T2_DQS_35)
/GPIO_18: J2.25, U1.F3 (IO_L14N_T2_SRCC_35)
/GPIO_19: J2.26, U1.F4 (IO_L14P_T2_SRCC_35)
/GPIO_20: J2.27, U1.F5 (IO_L13P_T2_MRCC_35)
/GPIO_21: J2.28, U1.G1 (IO_L17N_T2_35)
/GPIO_22: J2.29, U1.G2 (IO_L17P_T2_35)
/GPIO_23: J2.30, U1.G4 (IO_L16N_T2_35)
/GPIO_24: J2.33, U1.G5 (IO_L16P_T2_35)
/GPIO_25: J2.34, U1.H1 (IO_L20N_T3_35)
/GPIO_26: J2.35, U1.H2 (IO_L20P_T3_35)
/GPIO_27: J2.36, U1.H3 (IO_L21N_T3_DQS_35)
/GPIO_28: J3.3, U1.H4 (IO_L18N_T2_35)
/GPIO_29: J3.4, U1.H5 (IO_L18P_T2_35)
/GPIO_30: J3.5, U1.J1 (IO_L22N_T3_35)
/GPIO_31: J3.6, U1.J3 (IO_L21P_T3_DQS_35)
/GPIO_32: J3.7, U1.J4 (IO_L19N_T3_VREF_35)
/GPIO_33: J3.8, U1.J5 (IO_L19P_T3_35)
/GPIO_34: J3.9, U1.K1 (IO_L22P_T3_35)
/GPIO_35: J3.10, U1.K2 (IO_L24N_T3_35)
/GPIO_36: J3.13, U1.K3 (IO_L24P_T3_35)
/GPIO_37: J3.14, U1.K5 (IO_25_35)
/GPIO_38: J3.15, U1.L2 (IO_L23N_T3_35)
/GPIO_39: J3.16, U1.L3 (IO_L23P_T3_35)
/GPIO_40: J3.17, U1.L4 (IO_L1P_T0_34)
/GPIO_41: J3.18, U1.L5 (IO_0_34)
/GPIO_42: J3.19, U1.M1 (IO_L2N_T0_34)
/GPIO_43: J3.20, U1.M2 (IO_L2P_T0_34)
/GPIO_44: J3.23, U1.M4 (IO_L1N_T0_34)
/GPIO_45: J3.24, U1.M5 (IO_L6P_T0_34)
/GPIO_46: J3.25, U1.N1 (IO_L4P_T0_34)
/GPIO_47: J3.26, U1.N2 (IO_L3N_T0_DQS_34)
/GPIO_48: J3.27, U1.N3 (IO_L3P_T0_DQS_34)
/GPIO_49: J3.28, U1.N4 (IO_L6N_T0_VREF_34)
/GPIO_50: J3.29, U1.P1 (IO_L4N_T0_34)
/GPIO_51: J3.30, U1.P3 (IO_L5N_T0_34)
/GPIO_52: J3.33, U1.P4 (IO_L5P_T0_34)
/GPIO_53: J3.34, U1.P5 (IO_L10P_T1_34)
/GPIO_54: J3.35, U1.R1 (IO_L7N_T1_34)
/GPIO_55: J3.36, U1.R2 (IO_L7P_T1_34)
/IMAGE0: R60.1, SW1.1, U1.A3 (IO_L4N_T0_35)
/IMAGE1: R61.1, SW1.2, U1.B4 (IO_L4P_T0_35)
/INIT_B: R51.2, U1.K10 (INIT_B_0)
/JTAG_TCK: J4.3, U1.L7 (TCK_0)
/JTAG_TDI: J4.5, U1.N7 (TDI_0)
/JTAG_TDO: J4.6, U1.N8 (TDO_0)
/JTAG_TMS: J4.4, U1.M7 (TMS_0)
/MODE_M0: R53.2, U1.M9 (M0_0)
/MODE_M1: R54.1, U1.M10 (M1_0)
/MODE_M2: R55.1, U1.M11 (M2_0)
/POWER_GOOD: R10.2, U4.6 (PG)
/PROGRAM_B: R52.2, SW3.1, U1.L9 (PROGRAM_B_0)
/PROG_LED: R73.1, U1.A4 (IO_L3N_T0_DQS_AD5N_35)
/PUDC_B: R49.2, U1.L15 (IO_L3P_T0_DQS_PUDC_B_14)
/PWR_EN: C4.1, R1.2, SW2.1, U2.4 (EN)
/QSPI_CCLK: R45.2, U5.6 (CLK)
/QSPI_CCLK_FPGA: R45.1, U1.E8 (CCLK_0)
/QSPI_CS_B: R44.2, R46.2, U5.1 (~CS)
/QSPI_CS_B_FPGA: R44.1, U1.L12 (IO_L6P_T0_FCS_B_14)
/QSPI_IO0: R40.2, U5.5 (DI/IO_{0})
/QSPI_IO0_FPGA: R40.1, U1.J13 (IO_L1P_T0_D00_MOSI_14)
/QSPI_IO1: R41.2, U5.2 (DO/IO_{1})
/QSPI_IO1_FPGA: R41.1, U1.J14 (IO_L1N_T0_D01_DIN_14)
/QSPI_IO2: JP1.1 (A), R42.2, R47.2, U5.3 (~WP/IO_{2})
/QSPI_IO2_FPGA: R42.1, U1.K15 (IO_L2P_T0_D02_14)
/QSPI_IO3: R43.2, R48.2, U5.7 (~HOLD/~RESET/IO_{3})
/QSPI_IO3_FPGA: R43.1, U1.K16 (IO_L2N_T0_D03_14)
/USB_CC1: J1.A5 (CC1), R23.1
/USB_CC2: J1.B5 (CC2), R24.1
/USB_DM: R21.2, U1.B5 (IO_L2N_T0_AD12N_35)
/USB_DM_CONN: J1.A7 (D-), J1.B7 (D-), U6.3 (I/O2)
/USB_DM_PROT: R21.1, U6.4 (I/O2)
/USB_DP: R20.2, R22.2, U1.B6 (IO_L2P_T0_AD12P_35)
/USB_DP_CONN: J1.A6 (D+), J1.B6 (D+), U6.1 (I/O1)
/USB_DP_PROT: R20.1, U6.6 (I/O1)
/USB_INRUSH_CT: C2.1, U7.4 (CT)
/USB_PULLUP: R22.1, U1.B7 (IO_L1P_T0_AD4P_35)
/USB_QOD: R11.1, U7.5 (QOD)
/USB_SHIELD: C14.1, J1.SH (SHIELD), R27.1
/USER_LED0: R74.1, U1.A5 (IO_L3P_T0_DQS_AD5P_35)
/USER_LED1: R75.1, U1.A2 (IO_L8N_T1_AD14N_35)
/VBUS: C15.1, F1.1, J1.A4 (VBUS), J1.A9 (VBUS), J1.B4 (VBUS), J1.B9 (VBUS), R25.1, U6.5 (VBUS)
/VBUS_FUSED: C1.1, C2.2, F1.2, U7.1 (VIN), U7.3 (ON)
/VBUS_SENSE: R25.2, R26.1, U1.A7 (IO_L1N_T0_AD4N_35)
/VREFN_AGND: R59.2, U1.H7 (VREFN_0)
/VREFP_AGND: R58.2, U1.J8 (VREFP_0)

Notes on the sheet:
U2: +1V0
+3V3 decoupling
FPGA POWER / UG483 DECOUPLING
U3: +1V8
FPGA CONFIGURATION / MULTIBOOT
All VCCO banks are 3.3V. VREFP/VREFN use internal XADC reference via AGND.
USER I/O: BANKS 34/35, 3.3V
POWER: USB 5V -> 1.0V -> 1.8V -> 3.3V
+1V0 decoupling
U4: +3V3
+1V8 decoupling
NATIVE USB FULL-SPEED

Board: 4 copper layers, 136 parts (24 on the bottom side), 126 nets, no tracks yet.
